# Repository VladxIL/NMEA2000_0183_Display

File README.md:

# NMEA2000_0183_Display
Display NMEA2000 and NMEA0183 on DWIN 7" Display

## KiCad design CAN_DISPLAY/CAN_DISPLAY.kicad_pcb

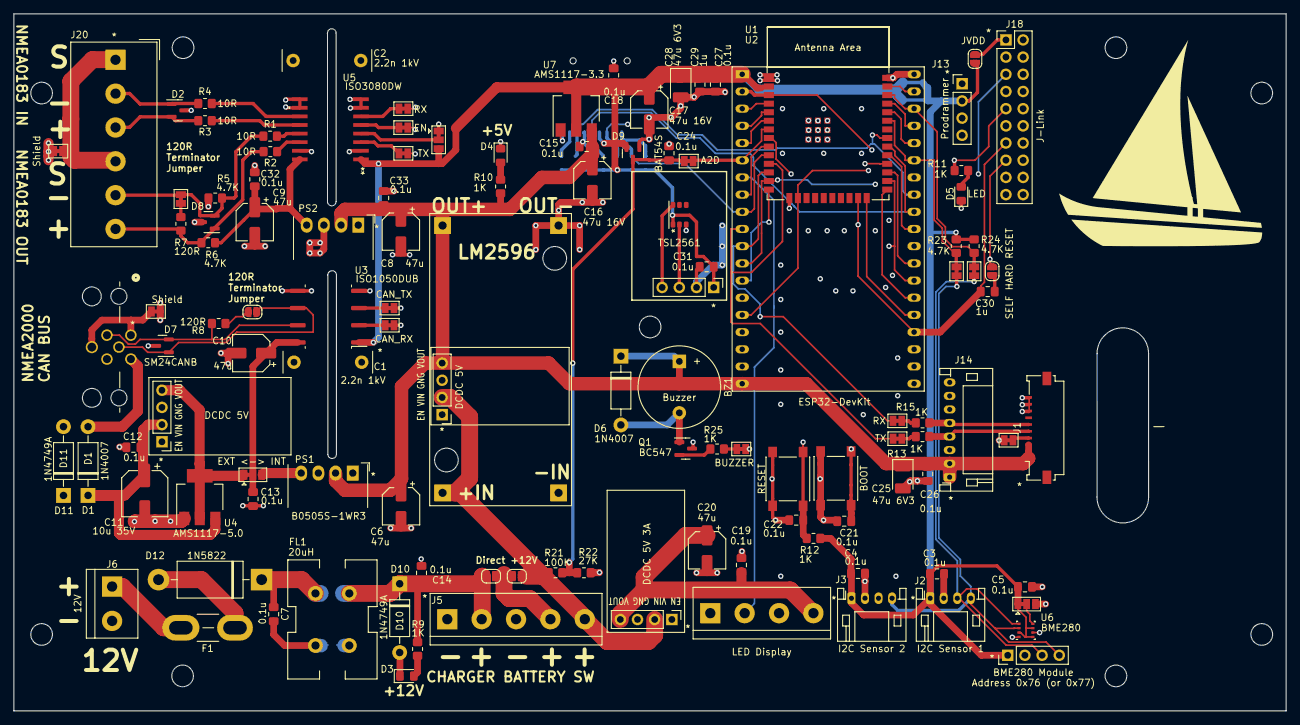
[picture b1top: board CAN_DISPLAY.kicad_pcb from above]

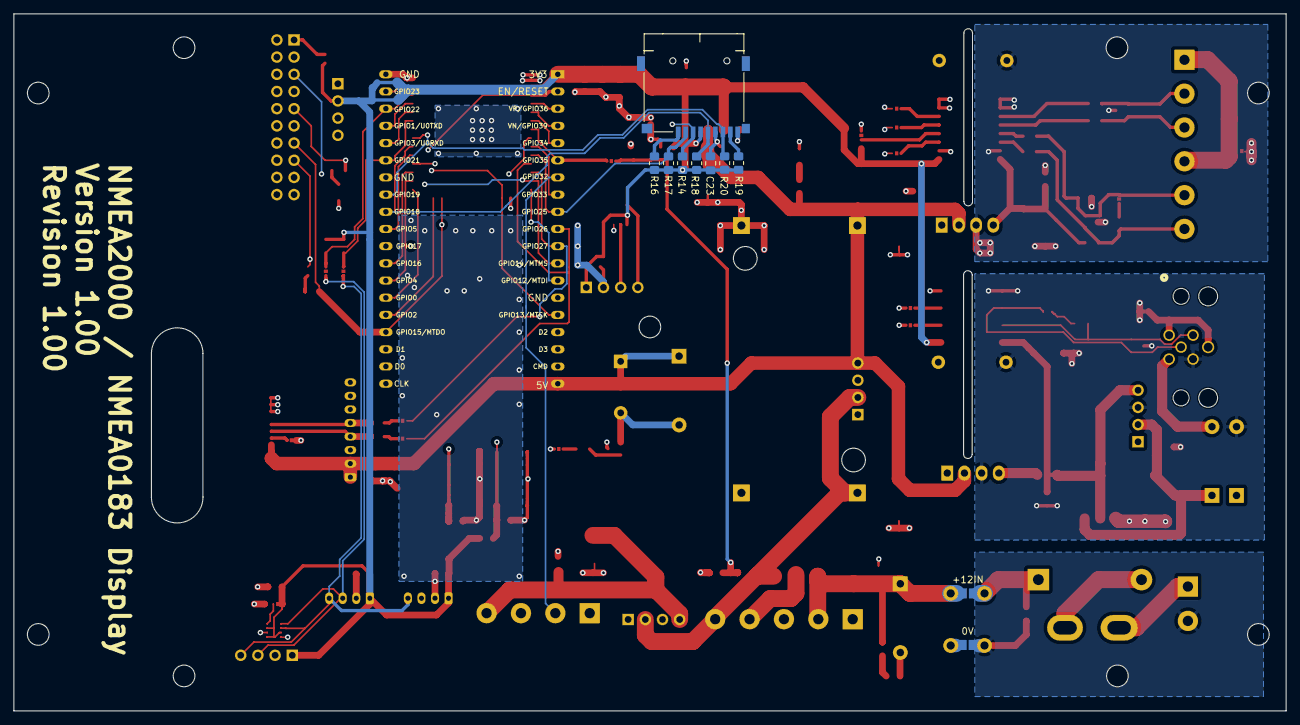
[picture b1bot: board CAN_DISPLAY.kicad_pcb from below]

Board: 4 copper layers, 188.0 x 103.0 mm, 129 parts (10 on the bottom side), 85 nets.

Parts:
BZ1: Buzzer; Buzzer_12x9.5RM7.6
C1, C2: 2.2n 1kV; C_Rect_L13.0mm_W3.0mm_P10.00mm_FKS3_FKP3_MKS4
C3, C4, C5, C7, C12, C13, C14, C15, C18, C19, C21, C22, C23, C24, C26, C27, C31, C32, C33: 0.1u; C_0805_2012Metric_Pad1.18x1.45mm_HandSolder
C6, C8, C9, C10, C20: 47u; CP_Elec_5x5.8
C11: 10u 35V; CP_Elec_6.3x4.5
C16, C17: 47u 16V; CP_Elec_5x5.8
C25, C28: 47u 6V3; CP_EIA-3528-21_Kemet-B_Pad1.50x2.35mm_HandSolder
C29, C30: 1u; C_0805_2012Metric_Pad1.18x1.45mm_HandSolder
D1, D6: 1N4007; D_DO-41_SOD81_P10.16mm_Horizontal
D2, D8: ESD SOT23; SOT-23
D3: 12V; LED_0805_2012Metric_Pad1.15x1.40mm_HandSolder
D4: 5V; LED_0805_2012Metric_Pad1.15x1.40mm_HandSolder
D5: LED; LED_0805_2012Metric_Pad1.15x1.40mm_HandSolder
D7: SM24CANB; SOT-23
D9: BAT54S; SOT-23
D10, D11: 1N4749A; D_DO-41_SOD81_P10.16mm_Horizontal
D12: 1N5822; D_DO-201AD_P15.24mm_Horizontal
F1: Fuse; Fuse_Blade_Mini_directSolder
FL1: 20uH; L_CommonMode_Wuerth_WE-CMB-S
J1: DISPLAY; Molex_200528-0100_1x10-1MP_P1.00mm_Horizontal
J2: I2C Sensor 1; JST_PH_S4B-PH-K_1x04_P2.00mm_Horizontal
J3: I2C Sensor 2; JST_PH_S4B-PH-K_1x04_P2.00mm_Horizontal
J4: NMEA2000; CONN5_43-01199_Vlad
J5: Power; TerminalBlock_bornier-5_P5.08mm
J6: 12V; TerminalBlock_bornier-2_P5.08mm
J8, J9: DCDC 5V; PinHeader_1x04_P2.54mm_Vertical
J10: DCDC 5V 3A; PinHeader_1x04_P2.54mm_Vertical
J11: Micro_SD_Card; J_SD_Card-micro_socket_A
J13: Prodrammer; PinHeader_1x04_P2.54mm_Vertical
J14: Display; JST_PH_S8B-PH-K_1x08_P2.00mm_Horizontal
J15: LED Display; TerminalBlock_bornier-4_P5.08mm
J16: BME280 Module; PinHeader_1x04_P2.54mm_Vertical
J18: J-Link; PinHeader_2x10_P2.54mm_Vertical
J19: TSL2561; PinHeader_1x04_P2.54mm_Vertical
J20: NMEA0183; Altech_AK300_1x06_P5.00mm_45-Degree
JP1: OPT; SolderJumper-2_P1.3mm_Bridged_Pad1.0x1.5mm
JP2: EXT <-> INT; SolderJumper-3_P1.3mm_Bridged12_Pad1.0x1.5mm
JP3, JP5: Shield; SolderJumper-2_P1.3mm_Bridged_Pad1.0x1.5mm
JP4: Address 0x76 (or 0x77); SolderJumper-3_P1.3mm_Bridged12_Pad1.0x1.5mm
JP6: *RE; SolderJumper-3_P1.3mm_Bridged12_Pad1.0x1.5mm
JP7: EN; SolderJumper-2_P1.3mm_Bridged_Pad1.0x1.5mm
JP8, JP10: TX; SolderJumper-2_P1.3mm_Bridged_Pad1.0x1.5mm
JP9, JP11: RX; SolderJumper-2_P1.3mm_Bridged_Pad1.0x1.5mm
JP12: SDA; SolderJumper-2_P1.3mm_Bridged_Pad1.0x1.5mm
JP13: SCK; SolderJumper-2_P1.3mm_Bridged_Pad1.0x1.5mm
JP14: CAN_TX; SolderJumper-2_P1.3mm_Bridged_Pad1.0x1.5mm
JP15: CAN_RX; SolderJumper-2_P1.3mm_Bridged_Pad1.0x1.5mm
JP16: +12IN; NOSILK SolderJumper-2_P1.3mm_Open_Pad1.0x1.5mm
JP17: 0V; NOSILK SolderJumper-2_P1.3mm_Open_Pad1.0x1.5mm
JP18: 120R; SolderJumper-2_P1.3mm_Bridged_Pad1.0x1.5mm
JP19, JP23, JP25: Open; SolderJumper-2_P1.3mm_Open_RoundedPad1.0x1.5mm
JP20: SELF HARD RESET; SolderJumper-2_P1.3mm_Open_RoundedPad1.0x1.5mm
JP21: JVDD; SolderJumper-2_P1.3mm_Open_RoundedPad1.0x1.5mm
JP22: A2D; SolderJumper-2_P1.3mm_Bridged_Pad1.0x1.5mm
JP24: BUZZER; SolderJumper-2_P1.3mm_Bridged_Pad1.0x1.5mm
LED1: TSL2561
PS1, PS2: B0505S-1WR3; Converter_DCDC_Murata_MEE1SxxxxSC_THT
PS3: LM2596; LM2596Module2
Q1: BC547; SOT-23
R1, R2, R3, R4: 10R; R_0805_2012Metric_Pad1.20x1.40mm_HandSolder
R5, R6, R23, R24: 4.7K; R_0805_2012Metric_Pad1.20x1.40mm_HandSolder
R7, R8: 120R; R_0805_2012Metric_Pad1.20x1.40mm_HandSolder
R9, R10, R11, R12, R13, R15, R25: 1K; R_0805_2012Metric_Pad1.20x1.40mm_HandSolder
R14, R16, R17, R18, R19, R20: 47K; R_0805_2012Metric_Pad1.20x1.40mm_HandSolder
R21: 100K; R_0805_2012Metric_Pad1.20x1.40mm_HandSolder
R22: 27K; R_0805_2012Metric_Pad1.20x1.40mm_HandSolder
SW1: BOOT; SW_Push_1P1T_NO_6x6mm_H9.5mm
SW2: RESET; SW_Push_1P1T_NO_6x6mm_H9.5mm
U1: ESP32-DevKit; ESP32-DevKitC
U2: ESP32-WROOM-E; ESP32-WROOM-32E
U3: ISO1050DUB; SOP-8_6.62x9.15mm_P2.54mm
U4: AMS1117-5.0; SOT-223-3_TabPin2
U5: ISO3080DW; DW16
U6: BME280; Bosch_LGA-8_2.5x2.5mm_P0.65mm_ClockwisePinNumbering
U7: AMS1117-3.3; SOT-223-3_TabPin2

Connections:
+3V3: C3.1, C4.1, C5.1, C17.1, C18.1, C23.1, C27.1, C28.1, C29.1, C31.1, D9.2 (K), J2.1, J3.1, J11.4 (VDD), J13.2, J16.1, J19.1, JP4.1 (A), JP6.3 (B), JP21.1 (A), LED1.1 (VDD), R12.2, R14.2, R16.2, R17.2, R18.2, R19.1, R20.1, R23.2, R24.2, U1.1 (3V3), U2.2 (3V3), U3.1 (VCC1), U5.1 (VCC1), U6.2 (CSB), U6.6 (VDDIO), U6.8 (VDD), U7.2 (VO)
+5V: BZ1.1 (-), C6.1, C8.1, C15.1, C16.1, C25.1, C26.1, C33.1, D6.1 (K), J1.1, J1.2, J1.3, J8.4, J14.1, J14.2, PS1.2 (+Vin), PS2.2 (+Vin), PS3.4 (+Vout), R10.2, U1.19 (5V), U7.3 (VI)
+5VA: C9.1, C32.1, PS2.4 (+Vout), R6.2, U5.16 (VCC2)
+5VD: C10.1, C13.1, JP2.2 (C), U3.8 (VCC2)
+5VP: C19.1, C20.1, J10.4, J15.4
+12V: J5.5, J8.2, J10.2, JP25.1 (A), PS3.2 (+Vin), R21.2
/Display/DWIN RX: J1.6, J14.5, R15.1
/Display/DWIN TX: J1.5, J14.4, R13.2
/ESP32/EN: C22.2, J18.15, JP20.1 (A), R12.1, SW2.2, U1.2 (CHIP_PU), U2.3 (EN/CHIP_PU)
/ESP32/GPIO_00_BOOT: C21.2, SW1.2, U1.25 (GPIO0/BOOT/ADC2_CH1), U2.25 (GPIO0/BOOT/ADC2_CH1)
/ESP32/GPIO_01_U0TXD: J13.4, U1.35 (U0TXD/GPIO1), U2.35 (U0TXD/GPIO1)
/ESP32/GPIO_02: U1.24 (ADC2_CH2/GPIO2), U2.24 (ADC2_CH2/GPIO2)
/ESP32/GPIO_03_U0RXD: J13.3, U1.34 (U0RXD/GPIO3), U2.34 (U0RXD/GPIO3)
/ESP32/GPIO_04: JP15.1 (A), U1.26 (ADC2_CH0/GPIO4), U2.26 (ADC2_CH0/GPIO4)
/ESP32/GPIO_05: JP14.1 (A), U1.29 (GPIO5), U2.29 (GPIO5)
/ESP32/GPIO_12: J18.5, U1.13 (MTDI/GPIO12/ADC2_CH5), U2.14 (MTDI/GPIO12/ADC2_CH5)
/ESP32/GPIO_13: J18.9, R11.2, U1.15 (MTCK/GPIO13/ADC2_CH4), U2.16 (MTCK/GPIO13/ADC2_CH4)
/ESP32/GPIO_14: J18.7, JP24.1 (A), U1.12 (MTMS/GPIO14/ADC2_CH6), U2.13 (MTMS/GPIO14/ADC2_CH6)
/ESP32/GPIO_15: C30.2, J18.13, JP7.1 (A), U1.23 (MTDO/GPIO15/ADC2_CH3), U2.23 (MTDO/GPIO15/ADC2_CH3)
/ESP32/GPIO_16: JP8.1 (A), U1.27 (GPIO16), U2.27 (GPIO16)
/ESP32/GPIO_17: JP9.1 (A), U1.28 (GPIO17), U2.28 (GPIO17)
/ESP32/GPIO_18: J11.5 (CLK), R18.1, U1.30 (GPIO18), U2.30 (GPIO18)
/ESP32/GPIO_19: J11.7 (DAT0), R20.2, U1.31 (GPIO19), U2.31 (GPIO19)
/ESP32/GPIO_21: JP12.1 (A), R23.1, U1.33 (GPIO21), U2.33 (GPIO21)
/ESP32/GPIO_22: JP13.1 (A), R24.1, U1.36 (GPIO22), U2.36 (GPIO22)
/ESP32/GPIO_23: J11.3 (CMD), R14.1, U1.37 (GPIO23), U2.37 (GPIO23)
/ESP32/GPIO_25: J11.2 (DAT3/CD), R17.1, U1.9 (DAC_1/ADC2_CH8/GPIO25), U2.10 (DAC_1/ADC2_CH8/GPIO25)
/ESP32/GPIO_26: JP10.1 (A), U1.10 (DAC_2/ADC2_CH9/GPIO26), U2.11 (DAC_2/ADC2_CH9/GPIO26)
/ESP32/GPIO_27: JP11.1 (A), U1.11 (ADC2_CH7/GPIO27), U2.12 (ADC2_CH7/GPIO27)
/ESP32/GPIO_32_32K: J15.2, U1.7 (32K_XP/GPIO32/ADC1_CH4), U2.8 (32K_XP/GPIO32/ADC1_CH4)
/ESP32/GPIO_33_32K: J15.3, U1.8 (32K_XN/GPIO33/ADC1_CH5), U2.9 (32K_XN/GPIO33/ADC1_CH5)
/ESP32/GPIO_34: U1.5 (VDET_1/GPIO34/ADC1_CH6), U2.6 (GPIO34/ADC1_CH6)
/ESP32/GPIO_35: JP22.1 (A), U1.6 (VDET_2/GPIO35/ADC1_CH7), U2.7 (GPIO35/ADC1_CH7)
/ESP32/GPIO_36: U1.3 (SENSOR_VP/GPIO36/ADC1_CH0), U2.4 (SENSOR_VP/GPIO36/ADC1_CH0)
/ESP32/GPIO_39: U1.4 (SENSOR_VN/GPIO39/ADC1_CH3), U2.5 (SENSOR_VN/GPIO39/ADC1_CH3)
/Isolated/NMEA IN+: D2.2 (K), J20.3, R3.2
/Isolated/NMEA IN-: D2.1 (K), J20.2, R4.2
/Isolated/NMEA OUT+: D8.1 (K), J20.6, R2.2, R6.1, R7.2
/Isolated/NMEA OUT-: D8.2 (K), J20.5, JP18.2 (B), R1.2, R5.2
/PowerSuply/12V_FL: C14.1, D10.1 (K), FL1.2, J5.2, JP16.1 (A), JP23.2 (B), R9.2
A2D_12V: C24.1, D9.3 (COM), JP22.2 (B), R21.1, R22.2
BUZZER: JP24.2 (B), R25.2
CANBUS_TO_RX: JP15.2 (B), U3.2 (RXD)
CANBUS_TO_TX: JP14.2 (B), U3.3 (TXD)
GND: C1.1, C2.1, C3.2, C4.2, C5.2, C6.2, C8.2, C14.2, C15.2, C16.2, C17.2, C18.2, C19.2, C20.2, C21.1, C22.1, C23.2, C24.2, C25.2, C26.2, C27.2, C28.2, C29.2, C31.2, C33.2, D3.1 (K), D4.1 (K), D5.1 (K), D9.1 (A), D10.2 (A), FL1.3, J1.8, J1.9, J1.10, J2.2, J3.2, J5.1, J5.3, J8.3, J10.3, J11.6 (VSS), J11.9 (SHIELD), J13.1, J14.7, J14.8, J15.1, J16.2, J18.6, J18.8, J18.10, J18.12, J18.14, J19.2, JP1.1 (A), JP4.3 (B), JP6.1 (A), JP17.1 (A), LED1.3 (GND), PS1.1 (-Vin), PS2.1 (-Vin), PS3.1 (-Vin), PS3.3 (-Vout), Q1.3 (E), R22.1, SW1.1, SW2.1, U1.14 (GND), U1.32 (GND), U1.38 (GND), U2.1 (GND), U2.15 (GND), U2.38 (GND), U2.39 (GND_THERMAL), U3.4 (GND1), U5.2 (GND1), U5.7 (GND1), U5.8 (GND1), U6.1 (GND), U6.7 (GND), U7.1 (GND)
GND2: C1.2, C10.2, C11.2, C12.2, C13.2, D7.3 (A), D11.2 (A), J4.3, J9.3, JP3.2 (B), PS1.3 (-Vout), U3.5 (GND2), U4.1 (GND)
GND3: C2.2, C9.2, C32.2, D2.3 (A), D8.3 (A), JP5.2 (B), PS2.3 (-Vout), R5.1, U5.9 (GND2), U5.10 (GND2), U5.15 (GND2)
GNDPWR: C7.2, FL1.4, J6.2, JP17.2 (B)
I2C_SCL: J2.3, J3.3, J16.3, J19.3, JP13.2 (B), LED1.2 (SCL), U6.4 (SCK)
I2C_SDA: J2.4, J3.4, J16.4, J19.4, JP12.2 (B), LED1.6 (SDA), U6.3 (SDI)
NMEA0183_Enable: JP7.2 (B), U5.5 (DE)
unnamed: BZ1.2 (+), D6.2 (A), Q1.1 (C)
unnamed: D1.2 (A), J4.2
unnamed: C11.1, C12.1, D1.1 (K), D11.1 (K), J9.2, U4.3 (VI)
unnamed: D3.2 (A), R9.1
unnamed: D4.2 (A), R10.1
unnamed: D5.2 (A), R11.1
unnamed: D12.2 (A), F1.2
unnamed: C7.1, D12.1 (K), FL1.1, JP16.2 (B)
unnamed: J1.4, JP1.2 (B)
unnamed: J5.4, JP23.1 (A), JP25.2 (B)
unnamed: F1.1, J6.1
unnamed: J9.4, JP2.1 (A), U4.2 (VO)
unnamed: J11.8 (DAT1), R19.2
unnamed: J11.1 (DAT2), R16.1
unnamed: J18.1, JP21.2 (B)
unnamed: J20.1, J20.4, JP5.1 (A)
unnamed: JP2.3 (B), PS1.4 (+Vout)
unnamed: J4.1, J4.6, JP3.1 (A)
unnamed: JP4.2 (C), U6.5 (SDO)
unnamed: JP6.2 (C), U5.4 (*RE)
unnamed: JP18.1 (A), R7.1
unnamed: D7.1 (K), J4.5, JP19.1 (A), U3.6 (CANL)
unnamed: JP19.2 (B), R8.1
unnamed: C30.1, JP20.2 (B)
unnamed: Q1.2 (B), R25.1
unnamed: D7.2 (K), J4.4, R8.2, U3.7 (CANH)
unnamed: R2.1, U5.14 (A)
unnamed: R1.1, U5.13 (B)
unnamed: R4.1, U5.11 (Y)
unnamed: R3.1, U5.12 (Z)
RX_DISPLAY_TX: JP11.2 (B), R15.2
RX_NMEA0183_TX: JP9.2 (B), U5.6 (D)
TX_DISPLAY_RX: JP10.2 (B), R13.1
TX_NMEA0183_RX: JP8.2 (B), U5.3 (R)

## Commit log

2023-11-12 Start
2023-11-12 KiCad Project
2023-11-12 Schema PDF file
2023-11-12 Step File
2023-11-13 PCB Fixes
2023-11-13 Add Ambient Light
2023-11-14 Added Light Sensor
2023-11-15 Add SW
2023-11-15 Comments CAN bus Power
2023-11-15 Release Version 1.00 Rev 1.00
2023-11-15 Gerber files
2023-11-17 Added Led Matrix project
2023-11-18 added esp32
2023-11-19 LED MX Release candidate
2023-11-20 Added BOM and Gerber files
2023-12-12 Added Board Test
2023-12-12 Added I2C sensors tests to board test FW
2023-12-12 Test Board FW Added VIN check
2025-01-25 1234
